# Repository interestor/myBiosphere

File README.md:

# myBiosphere
It is open source project that make device to make closed ecosystem on a desktop.

parts and material list is here.
http://archive.fabacademy.org/archives/2017/fablabkitakagaya/students/210/final_project.html

<br />

## files 
- code for Arduino[myBiosphere_Arduino.ino]
- code for Processing[myBiosphere_Processing.pde]
- processor boad design
- power board design
- stand's 3d design file
- branch's 3d design file
- island(pod)'s 3d design file
- cap's 3d design file
- heater's mould 3d design file
- ring's 3d design file

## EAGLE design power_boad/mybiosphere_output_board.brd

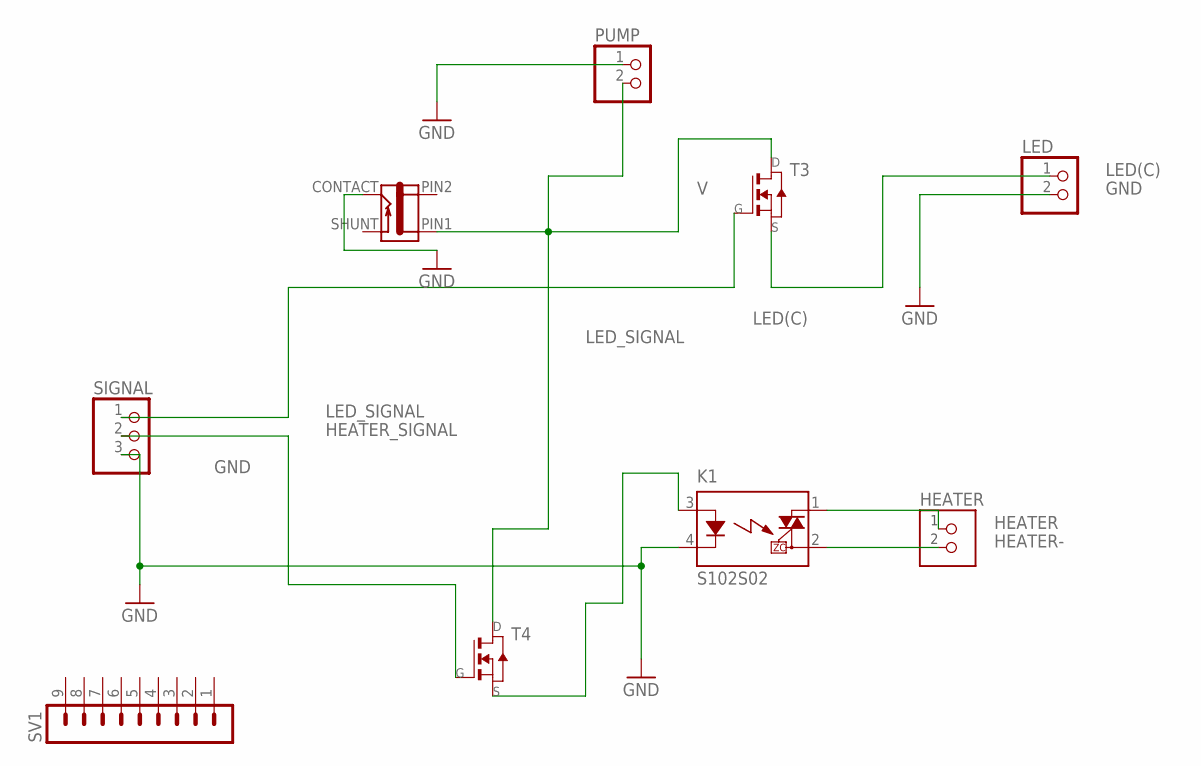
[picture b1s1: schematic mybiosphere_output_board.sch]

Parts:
HEATER: TERM-1X02-FABLAB; ED555DS-2DS
J1: JACK-2.1MM; PJ-002AH-SMT
K1: S102S02; S202S02
LED: PINHD-1X2/90; 1X02/90
PUMP: PINHD-1X2/90; 1X02/90
SIGNAL: PINHD-1X3; 1X03
SV1: MA09-1
T3, T4: NMOSFETTO252; TO252

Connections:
GND: J1.CONTACT, K1.4 (K), LED.2, PUMP.1, SIGNAL.3
HEATER: HEATER.1, K1.1 (DS1)
HEATER-: HEATER.2, K1.2 (DS2)
HEATER_SIGNAL: SIGNAL.2, T4.1 (G)
LED(C): LED.1, T3.2 (S)
LED_SIGNAL: SIGNAL.1, T3.1 (G)
unnamed: K1.3 (A), T4.2 (S)
PIN2: J1.PIN2
SHUNT: J1.SHUNT
V: J1.PIN1, PUMP.2, T3.3 (D), T4.3 (D)

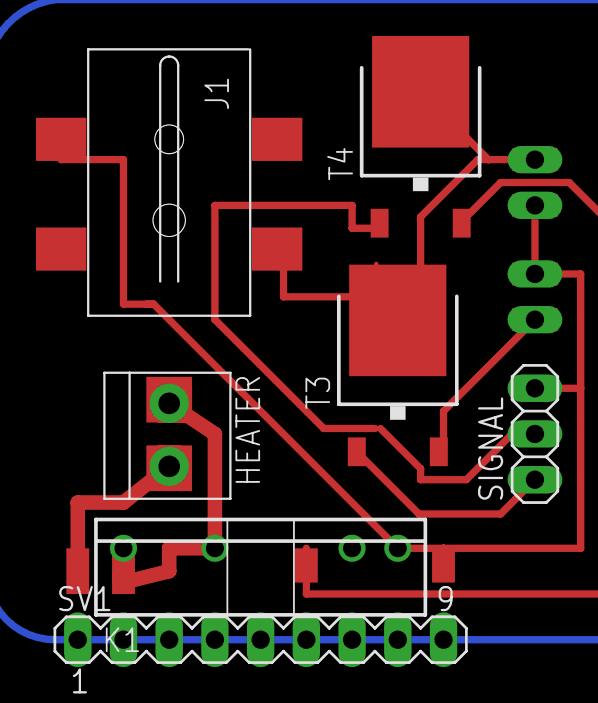
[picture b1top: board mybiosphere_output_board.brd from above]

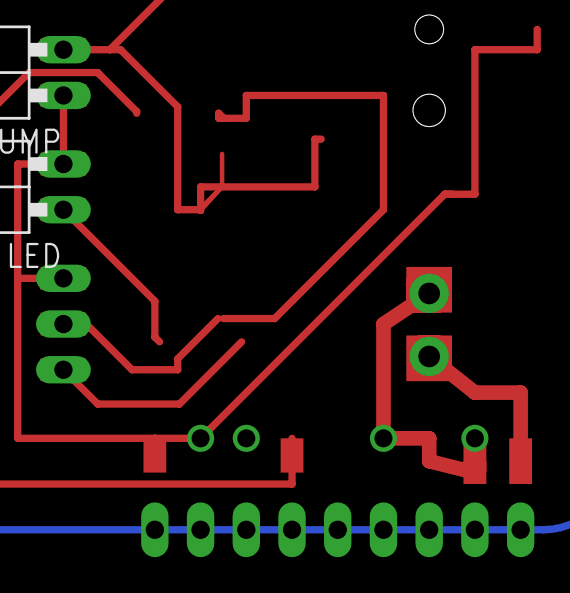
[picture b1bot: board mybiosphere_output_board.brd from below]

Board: 2 copper layers, 9 parts (2 on the bottom side), 8 nets.

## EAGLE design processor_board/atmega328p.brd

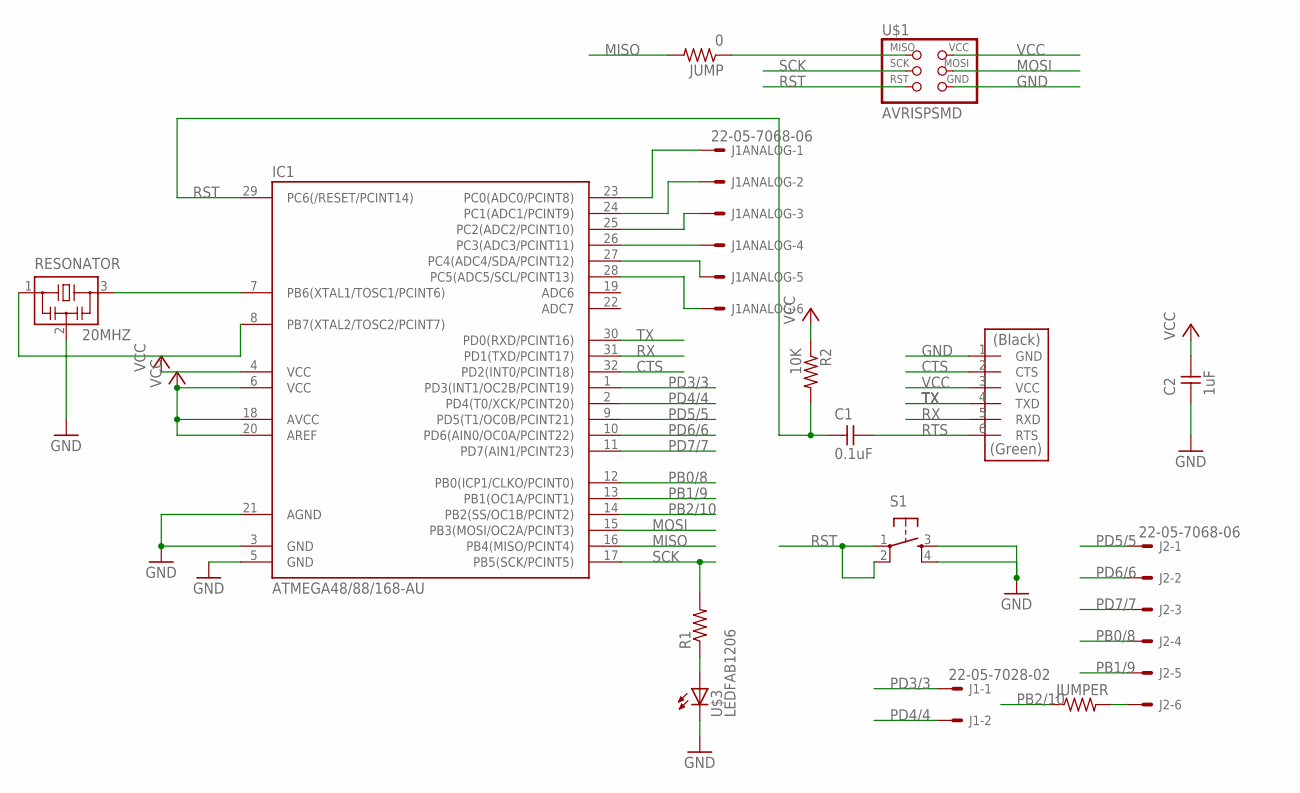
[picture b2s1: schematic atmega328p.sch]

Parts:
C1: 0.1uF; C1206FAB
C2: 1uF; C1206FAB
IC1: ATMEGA48/88/168-AU; TQFP32-08
J1: 22-05-7028-02; 7395-02
J1ANALOG, J2: 22-05-7068-06; 7395-06
JUMP: 0; R1206FAB
JUMPER: RES-US1206FAB; R1206FAB
R1: RES-US1206FAB; R1206FAB
R2: 10K; R1206FAB
RESONATOR: 20MHZ; EFOBM
S1: 6MM_SWITCH6MM_SWITCH; 6MM_SWITCH
U$1: AVRISPSMD; 2X03SMD
U$2: FTDI-SMD-HEADER; 1X06SMD
U$3: LEDFAB1206; LED1206FAB

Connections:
CTS: IC1.32 (PD2(INT0/PCINT18)), U$2.2 (CTS)
GND: C2.1, IC1.3 (GND), IC1.5 (GND), IC1.21 (AGND), RESONATOR.2, S1.3 (S), S1.4 (S1), U$1.6 (GND), U$2.1 (GND), U$3.2 (C)
MISO: IC1.16 (PB4(MISO/PCINT4)), JUMP.2
MOSI: IC1.15 (PB3(MOSI/OC2A/PCINT3)), U$1.4 (MOSI)
unnamed: IC1.7 (PB6(XTAL1/TOSC1/PCINT6)), RESONATOR.3
unnamed: IC1.8 (PB7(XTAL2/TOSC2/PCINT7)), RESONATOR.1
unnamed: JUMP.1, U$1.1 (MISO)
unnamed: J2.6, JUMPER.2
unnamed: IC1.23 (PC0(ADC0/PCINT8)), J1ANALOG.1
unnamed: R1.1, U$3.1 (A)
unnamed: IC1.24 (PC1(ADC1/PCINT9)), J1ANALOG.2
unnamed: IC1.25 (PC2(ADC2/PCINT10)), J1ANALOG.3
unnamed: IC1.26 (PC3(ADC3/PCINT11)), J1ANALOG.4
unnamed: IC1.27 (PC4(ADC4/SDA/PCINT12)), J1ANALOG.5
unnamed: IC1.28 (PC5(ADC5/SCL/PCINT13)), J1ANALOG.6
PB0/8: IC1.12 (PB0(ICP1/CLKO/PCINT0)), J2.4
PB1/9: IC1.13 (PB1(OC1A/PCINT1)), J2.5
PB2/10: IC1.14 (PB2(SS/OC1B/PCINT2)), JUMPER.1
PD3/3: IC1.1 (PD3(INT1/OC2B/PCINT19)), J1.1
PD4/4: IC1.2 (PD4(T0/XCK/PCINT20)), J1.2
PD5/5: IC1.9 (PD5(T1/OC0B/PCINT21)), J2.1
PD6/6: IC1.10 (PD6(AIN0/OC0A/PCINT22)), J2.2
PD7/7: IC1.11 (PD7(AIN1/PCINT23)), J2.3
RST: C1.1, IC1.29 (PC6(/RESET/PCINT14)), R2.2, S1.1, S1.2 (P1), U$1.5 (RST)
RTS: C1.2, U$2.6 (RTS)
RX: IC1.31 (PD1(TXD/PCINT17)), U$2.5 (RXD)
SCK: IC1.17 (PB5(SCK/PCINT5)), R1.2, U$1.3 (SCK)
TX: IC1.30 (PD0(RXD/PCINT16)), U$2.4 (TXD)
VCC: C2.2, IC1.4 (VCC), IC1.6 (VCC), IC1.18 (AVCC), IC1.20 (AREF), R2.1, U$1.2 (VCC), U$2.3 (VCC)

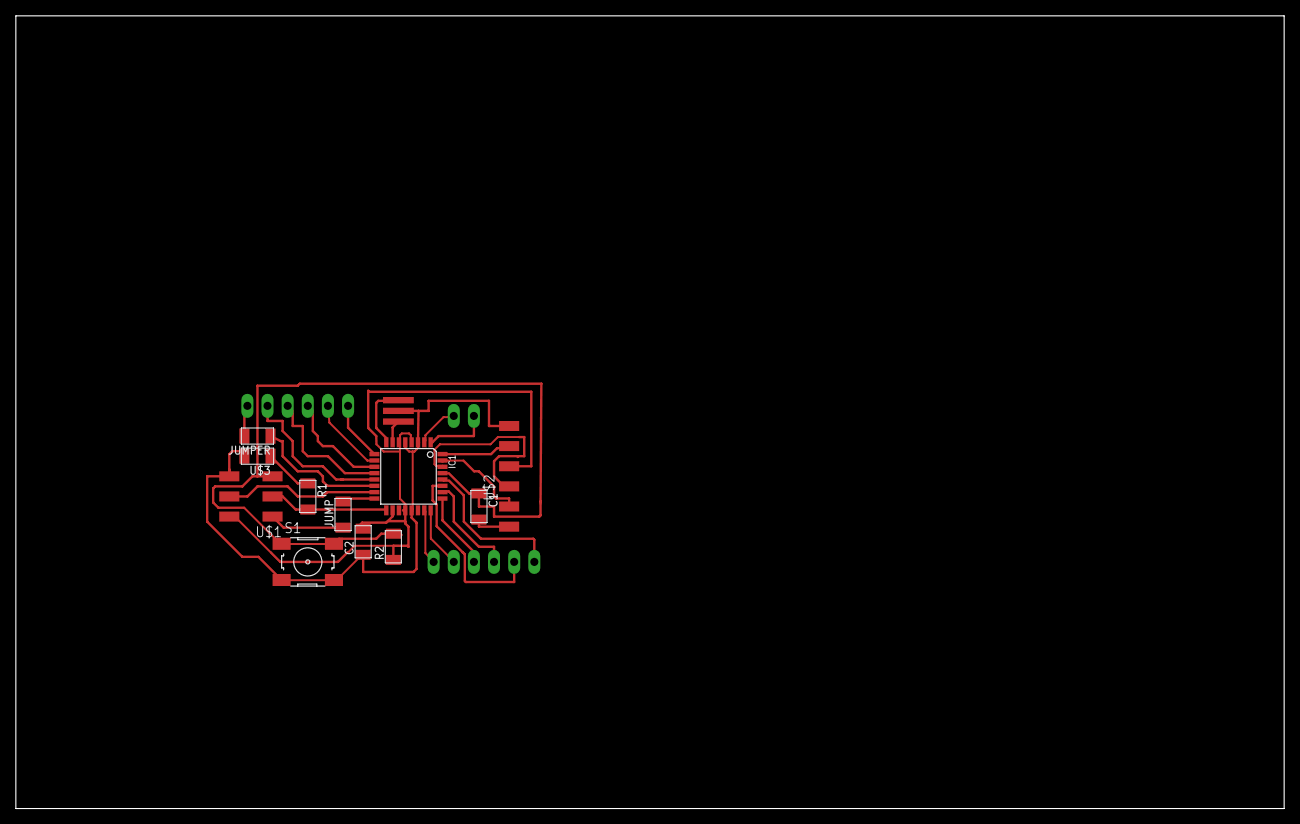
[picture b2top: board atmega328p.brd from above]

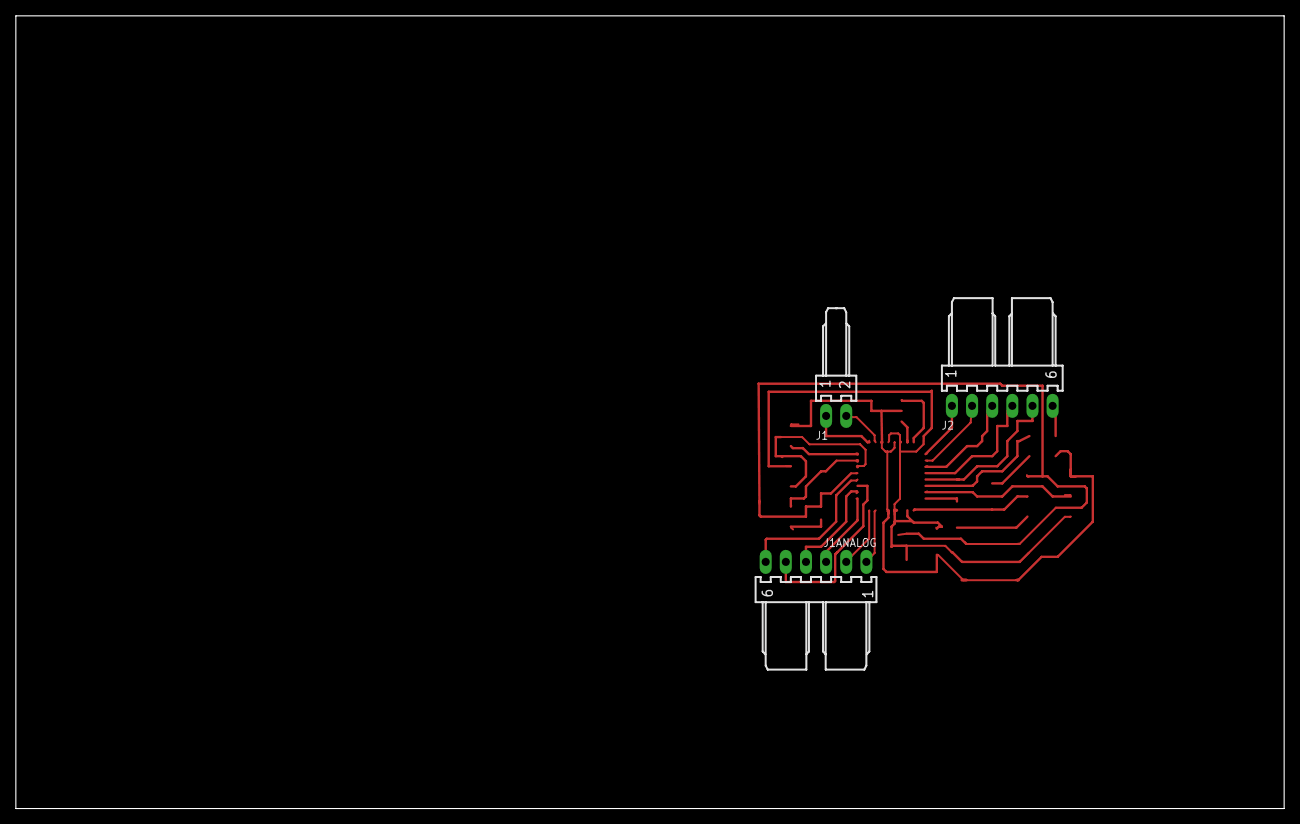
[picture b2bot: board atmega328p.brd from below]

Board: 2 copper layers, 160.0 x 100.0 mm, 15 parts (3 on the bottom side), 29 nets.

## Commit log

2017-06-27 Update README.md
    Add files list
2017-06-27 Update README.md
    Add filename
2017-06-27 Add initial files
    Add design files.These are files when I presented Fabacademy 2017.
2017-06-28 Update README.md
    Add license
2017-07-11 Add top_hole.ai
    Add file for ease cut top hole

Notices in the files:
README.md:
CC BY-NC-SA 4.0
